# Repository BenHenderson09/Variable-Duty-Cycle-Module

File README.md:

# Variable-Duty-Cycle-Module
A module which applies a square wave across a given component, with the duty cycle varied by a potentiometer.

## Details
- 555 timer controls the cycle.
- Capacitor C1 can be changed to alter the frequency.
- Duty cycle can be varied between 5% and 100%.
- All CAD files available [here.](https://github.com/BenHenderson09/Variable-Duty-Cycle-Module/tree/master/kicad)

## Schematic

## Waveform example

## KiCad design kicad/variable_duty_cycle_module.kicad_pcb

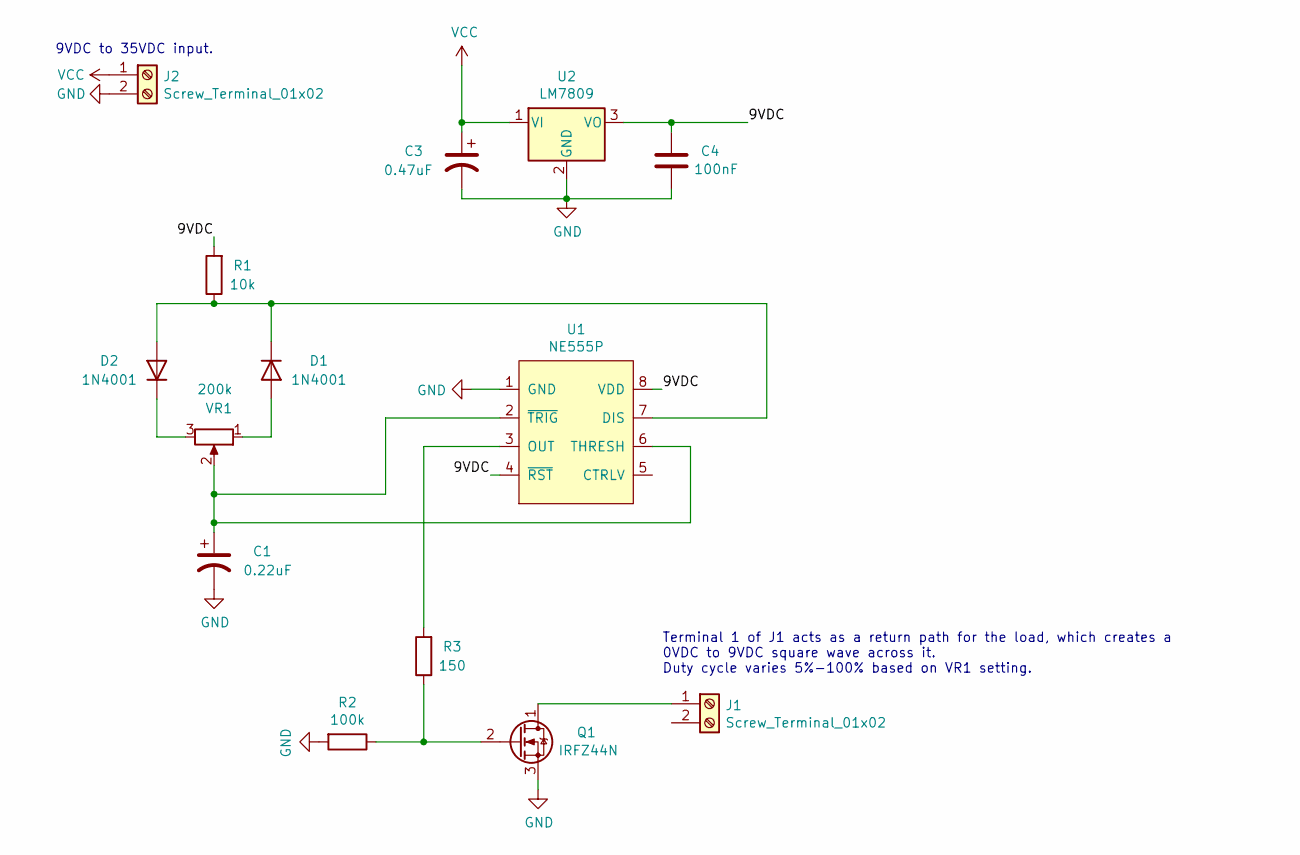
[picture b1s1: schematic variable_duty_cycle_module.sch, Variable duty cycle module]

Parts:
C1: 0.22uF; CP_Radial_D4.0mm_P2.00mm
C3: 0.47uF; CP_Radial_D4.0mm_P2.00mm
C4: 100nF; C_Disc_D6.0mm_W2.5mm_P5.00mm
D1, D2: 1N4001; D_DO-41_SOD81_P10.16mm_Horizontal
J1, J2: Screw_Terminal_01x02; TerminalBlock_Phoenix_MKDS-1,5-2-5.08_1x02_P5.08mm_Horizont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
Q1: IRFZ44N; TO-220-3_Vertical
R1: 10k; R_Axial_DIN0207_L6.3mm_D2.5mm_P7.62mm_Horizontal
R2: 100k; R_Axial_DIN0207_L6.3mm_D2.5mm_P7.62mm_Horizontal
R3: 150; R_Axial_DIN0207_L6.3mm_D2.5mm_P7.62mm_Horizontal
U1: NE555P; NE555P-DIP
U2: LM7809; TO-220-3_Vertical
VR1: 200k; Potentiometer_Piher_T-16H_Single_Horizontal

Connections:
/9VDC: C4.1, R1.2, U1.4 (~RST), U1.8 (VDD), U2.3 (VO)
GND: C1.2, C3.2, C4.2, J2.2, Q1.3, R2.2, U1.1 (GND), U2.2 (GND)
unnamed: C1.1, U1.2 (~TRIG), U1.6 (THRESH), VR1.2
unnamed: D1.1 (K), D2.2 (A), R1.1, U1.7 (DIS)
unnamed: D1.2 (A), VR1.1
unnamed: D2.1 (K), VR1.3
unnamed: J1.1, Q1.1
unnamed: Q1.2, R2.1, R3.1
unnamed: R3.2, U1.3 (OUT)
VCC: C3.1, J2.1, U2.1 (VI)

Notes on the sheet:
9VDC to 35VDC input.
Terminal 1 of J1 acts as a return path for the load, which creates a 0VDC to 9VDC square wave across it. Duty cycle varies 5%-100% based on VR1 setting.

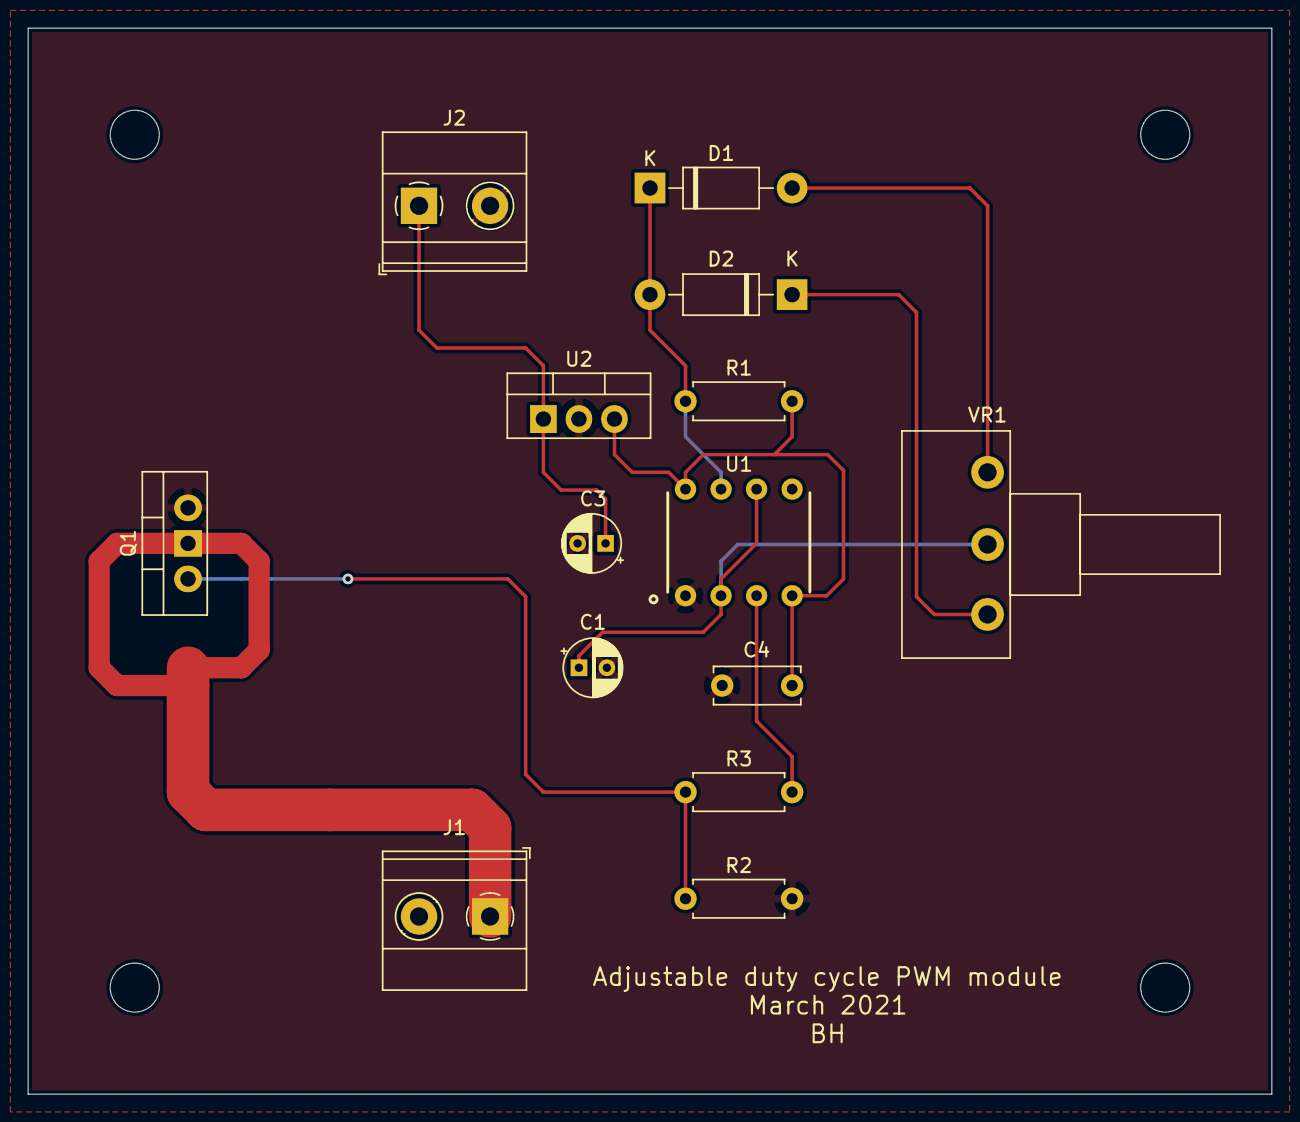
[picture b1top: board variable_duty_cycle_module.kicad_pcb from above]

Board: 2 copper layers, 88.9 x 76.2 mm, 14 parts (0 on the bottom side), 10 nets.

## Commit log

2021-04-08 Added KiCad files
2021-04-08 Added images
2021-04-09 Added README and schematic
2021-04-09 Fixed file extension
2021-04-10 Added waveforms
